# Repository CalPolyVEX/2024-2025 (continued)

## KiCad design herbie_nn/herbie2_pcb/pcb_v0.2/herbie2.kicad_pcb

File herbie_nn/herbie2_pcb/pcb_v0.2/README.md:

# Pinout

PA02 - unused analog input (A0)

PA04 - servo 3

PA05 - input voltage measurement

PA06 - right motor PWM

PA07 - left motor PWM

PA15 - servo 1

PA16 - left motor direction

PA17 - encoder 2 slave select

PA18 - right motor direction

PA19 - encoder 1 slave select

PA20 - servo 2

PA21 - servo 0

PB02 - unused analog input (A5)

PB08 - unused analog input (A1)

PB09 - unused analog input (A2)

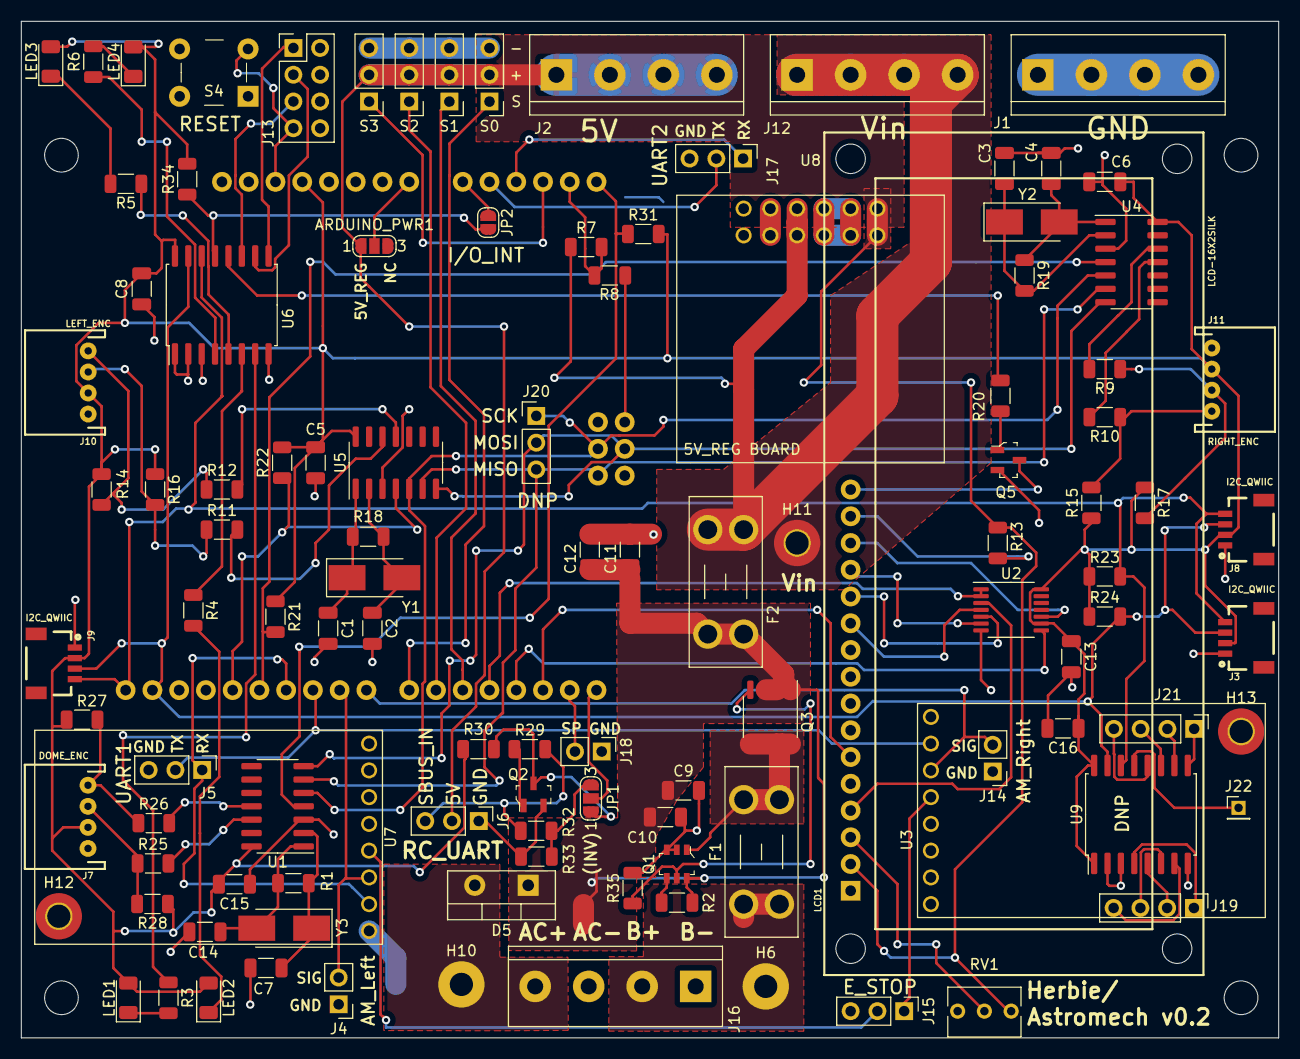
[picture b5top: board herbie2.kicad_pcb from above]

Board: 2 copper layers, 119.4 x 96.5 mm, 116 parts (1 on the bottom side), 92 nets.

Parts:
ARDUINO_PWR1: SolderJumper_3_Open; SolderJumper-3_P1.3mm_Open_RoundedPad1.0x1.5mm_NumberLabels
B2: ARDUINO_UNO_R3_SHIELD_ICSP; UNO_R3_SHIELD_ICSP
C1, C2, C3, C4, C7, C14: 12pF; C_1206_3216Metric
C5, C6, C8, C9, C13, C15, C16: .1uF; C_1206_3216Metric
C10: 1uF; C_1206_3216Metric
C11, C12: 10uF; C_1206_3216Metric
D5: CVFD20065A; TO-220-2_Vertical
F1, F2: Fuse; Fuseholder_Blade_Mini_Keystone_3568
H1, H2, H3, H4: MountingHole; MountingHole_3.2mm_M3_ISO7380
H6: PWR_BATT1; MountingHole_2.2mm_M2_Pad
H10: AC_PWR; MountingHole_2.2mm_M2_Pad
H11, H12, H13: MountingHole_Pad; MountingHole_2.2mm_M2_Pad_TopBottom
J1: GND; TerminalBlock_bornier-4_P5.08mm
J2: 5V; TerminalBlock_bornier-4_P5.08mm
J3, J8, J9: I2C_QWIIC; 1X04_1MM_RA
J4: AM_Left; PinHeader_1x02_P2.54mm_Vertical
J5: Conn_01x03_Female; PinHeader_1x03_P2.54mm_Vertical
J6: RC_UART; PinHeader_1x03_P2.54mm_Vertical
J7: DOME_ENC; JST-4-PTH
J10: LEFT_ENC; JST-4-PTH
J11: RIGHT_ENC; JST-4-PTH
J12: Vin; TerminalBlock_bornier-4_P5.08mm
J13: Conn_02x04_Odd_Even; PinHeader_2x04_P2.54mm_Vertical
J14: AM_Right; PinHeader_1x02_P2.54mm_Vertical
J15: Conn_01x03_Male; PinHeader_1x03_P2.54mm_Vertical
J16: Power; TerminalBlock_bornier-4_P5.08mm
J17, J20: Conn_01x03; PinHeader_1x03_P2.54mm_Vertical
J18: SmartPort; PinHeader_1x02_P2.54mm_Vertical
J19, J21: Conn_01x04_Female; PinHeader_1x04_P2.54mm_Vertical
J22: Conn_01x01; PinHeader_1x01_P2.00mm_Vertical
JP1: SolderJumper_3_Open; SolderJumper-3_P1.3mm_Open_RoundedPad1.0x1.5mm_NumberLabels
JP2: SolderJumper_2_Open; SolderJumper-2_P1.3mm_Open_RoundedPad1.0x1.5mm
LCD1: LCD-16X2SILK; LCD-16X2
LED1, LED2, LED3, LED4: LED; LED_1206_3216Metric
Q1: LTC4412; SOT-23-6
Q2, Q5: 2N7002; SOT-23-3
Q3: Si4427; SO-8_3.9x4.9mm_P1.27mm_Si4427
R1, R18, R19: 1M; R_1206_3216Metric
R2: 470K; R_1206_3216Metric
R3, R4, R5, R6: 330; R_1206_3216Metric
R7, R8: R; R_1206_3216Metric
R9, R10, R11, R12, R25, R26: 100; R_1206_3216Metric
R13: 10; R_1206_3216Metric
R14, R15, R16, R17, R21, R22, R27, R28, R31, R34: 20K; R_1206_3216Metric
R20, R29, R35: 1K; R_1206_3216Metric
R23, R24, R30, R32, R33: 4.7K; R_1206_3216Metric
RV1: 10K; Potentiometer_Bourns_3266Y_Vertical
S0: Servo0; PinHeader_1x03_P2.54mm_Vertical
S1: Servo1; PinHeader_1x03_P2.54mm_Vertical
S2: Servo2; PinHeader_1x03_P2.54mm_Vertical
S3: Servo3; PinHeader_1x03_P2.54mm_Vertical
S4: B3F-1000; Switch_Tactile_THT_B3F-1xxx
U1, U4, U5: LS7366R; SOIC-14_3.9x8.7mm_P1.27mm
U2: 74164; TSSOP-14_4.4x5mm_P0.65mm
U3, U7: 24v13_Pololu
U6, U9: TCA9534; SOIC-16W_7.5x10.3mm_P1.27mm
U8: D36V50F5_Pololu
Y1, Y2, Y3: 20MHz; Crystal_SMD_5032-2Pin_5.0x3.2mm_HandSoldering

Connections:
3.3V: B2.3.3V, C5.2, C6.2, C8.1, C13.1, C15.2, C16.1, J3.2, J7.2, J8.2, J9.2, J10.2, J11.2, LED1.2, LED2.2, LED3.2, LED4.2, R14.1, R15.1, R16.1, R17.1, R21.1, R22.2, R23.1, R24.1, R27.1, R28.1, R30.2, R31.2, R34.1, U1.14, U2.9, U2.14, U4.14, U5.14, U6.16, U9.1, U9.16
5V_REG: ARDUINO_PWR1.1, J2.1, J2.2, J2.3, J2.4, J6.2, LCD1.2, R13.1, RV1.1, S0.2, S1.2, S2.2, S3.2, U8.1
A0: B2.A0, JP2.1
AC_PWR: D5.2, H10.1, J16.4
ARD_VIN: ARDUINO_PWR1.2, B2.VIN
BATT1: F1.1, H6.1, J16.2
BATT1_F: F1.2, Q1.1, Q3.3
CLK_LCD: B2.D3, U2.8
DATA_LCD: B2.D4, U2.1, U2.2
DB4: LCD1.11, U2.4
DB5: LCD1.12, U2.5
DB6: LCD1.13, U2.6
DB7: LCD1.14, U2.10
DI0: J13.1, U6.9
DI1: J13.3, U6.10
DI2: J13.5, U6.11
ENC1_SS: B2.D12, R21.2, U4.4
ENC2_SS: B2.D13, R22.1, U5.4
ENC3_SS: B2.A5, R31.1, U1.4
ENC_MISO: B2.MISO, J20.3, U1.6, U4.6, U5.6
ENC_MOSI: B2.MOSI, J20.2, U1.7, U4.7, U5.7
ENC_SCK: B2.SCK, J20.1, U1.5, U4.5, U5.5
E_STOP1: J15.1, U3.4
E_STOP2: J15.2, U7.4
GND: B2.GND@, B2.GND_, C1.2, C2.2, C3.2, C4.2, C5.1, C6.1, C7.2, C8.2, C9.2, C10.2, C11.2, C12.2, C13.2, C14.2, C15.1, C16.2, H12.1, H13.1, J1.1, J1.2, J1.3, J1.4, J3.1, J4.1, J5.3, J6.1, J7.1, J8.1, J9.1, J10.1, J11.1, J13.2, J13.4, J13.6, J13.8, J14.1, J15.3, J16.1, J16.3, J17.3, J18.1, LCD1.1, LCD1.5, Q1.2, Q1.3, Q2.2, Q5.2, R8.2, R33.1, R35.2, RV1.3, S0.3, S1.3, S2.3, S3.3, S4.1, U1.3, U2.7, U3.1, U4.3, U5.3, U6.1, U6.2, U6.3, U6.8, U7.1, U8.2, U9.2, U9.3, U9.8
LCD_BL: R20.2, U6.12
LCD_E: B2.D2, LCD1.6
LCD_RS: LCD1.4, U2.3
MOTOR1_DIR: B2.D10, J5.2, U3.2
MOTOR1_PWM: B2.D8, J14.2, U3.3
MOTOR2_DIR: B2.D11, J5.1, U7.2
MOTOR2_PWM: B2.D9, J4.2, U7.3
unnamed: B2.A1, J17.2
unnamed: B2.A2, J17.1
unnamed: C1.1, R18.2, U5.1, Y1.1
unnamed: C2.1, R18.1, U5.2, Y1.2
unnamed: C3.1, R19.2, U4.2, Y2.1
unnamed: C4.1, R19.1, U4.1, Y2.2
unnamed: C7.1, R1.2, U1.2, Y3.1
unnamed: C14.1, R1.1, U1.1, Y3.2
unnamed: J7.3, R25.1, R28.2
unnamed: J7.4, R26.1, R27.2
unnamed: J10.3, R11.1, R16.2
unnamed: J10.4, R12.1, R14.2
unnamed: J11.3, R9.1, R17.2
unnamed: J11.4, R10.1, R15.2
unnamed: J19.1, U9.4
unnamed: J19.2, U9.5
unnamed: J19.3, U9.6
unnamed: J19.4, U9.7
unnamed: J21.1, U9.9
unnamed: J21.2, U9.10
unnamed: J21.3, U9.11
unnamed: J21.4, U9.12
unnamed: J22.1, U9.13
unnamed: JP1.1, Q2.3, R30.1
unnamed: JP2.2, R34.2, U6.13
unnamed: LCD1.3, RV1.2
unnamed: LCD1.15, R13.2
unnamed: LCD1.16, Q5.3
unnamed: LED1.1, R3.2
unnamed: LED2.1, R4.2
unnamed: LED3.1, R5.2
unnamed: LED4.1, R6.2
unnamed: Q1.4, R2.1
unnamed: Q1.5, Q3.1, R35.1
unnamed: Q2.1, R29.1
unnamed: Q5.1, R20.1
unnamed: R3.1, U6.7
unnamed: R4.1, U6.6
unnamed: R5.1, U6.5
unnamed: R6.1, U6.4
unnamed: R9.2, U4.12
unnamed: R10.2, U4.11
unnamed: R11.2, U5.12
unnamed: R12.2, U5.11
unnamed: R25.2, U1.12
unnamed: R26.2, U1.11
RESET: B2.RES, J13.7, S4.3
SBUS_IN: J6.3, R29.2, R32.2
SBUS_IN_SEL: B2.RX, JP1.2
SCL: B2.SCL, J3.4, J8.4, J9.4, R23.2, U6.14, U9.14
SDA: B2.SDA, J3.3, J8.3, J9.3, R24.2, U6.15, U9.15
SDIV: JP1.3, R32.1, R33.2
SERVO0: B2.D7, S0.1
SERVO1: B2.D5, S1.1
SERVO2: B2.D6, S2.1
SERVO3: B2.A3, S3.1
SMART_PORT: B2.TX, J18.2
VIN: F2.1, H11.1, J12.1, J12.2, J12.3, J12.4, R7.1, U8.3
VIN_FUSE: C9.1, C10.1, C11.1, C12.1, D5.1, F2.2, Q1.6, Q3.2, R2.2
VIN_MEASURE: B2.A4, R7.2, R8.1

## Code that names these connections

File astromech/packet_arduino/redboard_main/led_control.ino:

#include "led_control.h"

// LED Controller Uses Pin PA00 for RX and PA01 for TX

// Notes for PCB Connections:
// UART1 TX: D10 (PA18)
// UART1 RX: D11 (PA16)
// UART2 TX: A1 (PB08)
// UART2 RX: A2 (PB09)

// This Module Will Use UART2 TX with Sercom4, UART2 RX Will be Unused

// Data Transmission PseudoCode
// Have an Array of Size N Bytes to Contain the Data to be Transmitted
// This Array Should Have an Iterator That Contains the Current Byte to be Sent
// Upon Request to Send Packet, sendLEDCommand Will be Called.
// This Function Will Store The Data to be Transmitted, Its Size, Reset the Iterator, and Activate the First Byte to be Transmitted
// For Each Transmitted Byte that is Complete, an Interupt Will be Called, Requesting the Next Byte
// Increment the Iterator, but if Iterator Equals Packet Size, Stop Transmitting
// No Need for a Timer

// Array of Bytes
uint8_t transmit_bytes[8]{0};

// Index in Byte Array
uint8_t byte_index = 0;

// The Size of the Current Byte Packet
uint8_t packet_size = 0;

// Setup the USART for the LED Controller
void setupLED()
{
    PORT->Group[1].DIRSET.reg |= PORT_PB08;
    PORT->Group[1].OUTCLR.reg |= PORT_PB08;
    //PORT->Group[1].DIR.reg |= PORT_PB08;

    NVIC_DisableIRQ(SERCOM4_IRQn);

    // CLOCKING SERIAL
    GCLK->GENDIV.reg = GCLK_GENDIV_DIV(250) | // Divide the 48MHz clock source by divisor 1: 48MHz/1=48MHz
                       GCLK_GENDIV_ID(5);   // Select Generic Clock (GCLK) 5
    GCLK->GENCTRL.reg =
        GCLK_GENCTRL_IDC |
        GCLK_GENCTRL_GENEN |      // enable the clock connection to the peripheral(s)
        GCLK_GENCTRL_ID(5) |      // use clock gen 5
        GCLK_GENCTRL_SRC_DFLL48M; // Set Clock to 48 MHz
    GCLK->CLKCTRL.reg =
        GCLK_CLKCTRL_CLKEN |          // enable the clock
        GCLK_CLKCTRL_GEN_GCLK5 |      // enable generic clock generator 5
        GCLK_CLKCTRL_ID_SERCOM4_CORE; // set clock to SERCOM2_CORE

    SERCOM4->USART.CTRLA.bit.SWRST = 1; // do a software reset on the serial peripheral
    while (SERCOM4->USART.SYNCBUSY.bit.SWRST);

    // INITIALIZING PADS
    // initialize TX pin to be controlled by serial
    PORT->Group[1].PINCFG[8].bit.PMUXEN = 1; // designate RXPIN as controlled by a peripheral
    PORT->Group[1].PMUX[4].reg = PORT_PMUX_PMUXE_D; // set to use multiplexing D function

    
    
    // INITIALIZING SERIAL

    SERCOM4->USART.CTRLA.bit.MODE = 1;   // using internal clock
    SERCOM4->USART.CTRLA.bit.CMODE = 0;  // use asyncronous communication
    SERCOM4->USART.CTRLA.bit.SAMPR = 0x0;    // Set Serial to Arithmatic Mode
    SERCOM4->USART.CTRLA.bit.RXPO = 0x1; // Set Unused RX Pin to Pad[1]
    SERCOM4->USART.CTRLA.bit.TXPO = 0x0; // Set TX Pin to Pad[0]
    SERCOM4->USART.INTENCLR.bit.TXC = 0x1; // Set interupt to be disabled

    SERCOM4->USART.CTRLB.bit.CHSIZE = 0x0; // we have 8 bits of data per USART frame
    SERCOM4->USART.CTRLA.bit.DORD = 1;     // using MSB
    SERCOM4->USART.CTRLB.bit.SBMODE = 0x0; // using 1 stop bits
    SERCOM4->USART.BAUD.reg = 13107;       // Baud Rate for LED Controller is 9600
    SERCOM4->USART.CTRLB.bit.TXEN = 0x1;   // enable Serial TX
    SERCOM4->USART.CTRLB.bit.RXEN = 0x0; // turn RX pin off
    while (SERCOM4->USART.SYNCBUSY.bit.CTRLB); // wait for sync

    SERCOM4->USART.CTRLA.bit.ENABLE = 1; // enable the serial module

    while (SERCOM4->USART.SYNCBUSY.bit.ENABLE); // wait for syncronization

    // Enable the Transmit Complete Interupt
    NVIC_ClearPendingIRQ(SERCOM4_IRQn);                      // clear any incoming interrupt requests from SERCOM4
    NVIC_SetPriority(SERCOM4_IRQn, 0);                       // set highest priority for SERCOM4
    NVIC_EnableIRQ(SERCOM4_IRQn);                            // enable interrupt requests for SERCOM4
    SERCOM4->USART.INTENSET.reg = SERCOM_USART_INTENSET_TXC; // enable TXC interrupts for when recieving is complete

    // Reset Byte Index
    byte_index = 0;
}

// Send Command to LED Controller
void sendLEDCommand(uint8_t* package, uint8_t package_size)
{
    // Store Size of Package
    packet_size = package_size;

    // Copy Data of Package Parameter to Transmit Bytes Array
    //for (uint8_t* package_ptr = package, *bytes_ptr = transmit_bytes; package_ptr != package + packet_size; package_ptr++, bytes_ptr++)
    //    *bytes_ptr = *package_ptr;
    for (uint8_t i = 0; i < package_size; i++)
      transmit_bytes[i] = package[i];

    // Send First Byte
    SERCOM4->USART.DATA.bit.DATA = transmit_bytes[0];

    // Reset Byte Index
    byte_index = 1;
}

void SERCOM4_Handler()
{
    // Reset the Interupt Flag
    SERCOM4->USART.INTFLAG.bit.TXC = 0x1;
    PORT->Group[0].OUT.reg ^= PORT_PA17;

    // If Data is Still Left to be Transmitted, Transmit the Next Byte
    if (byte_index < packet_size)
    {
        SERCOM4->USART.DATA.bit.DATA = transmit_bytes[byte_index];
        byte_index++;
    }
}

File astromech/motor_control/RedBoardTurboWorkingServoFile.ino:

// C++ code
const uint32_t MOTOR_WAVELENGTH = 960000; //wavelength from peak to peak in Hz
const float MOTOR_BASE_TIME = 72000; //value in Hz of high length when speed = 0
const float MOTOR_CHANGE_CONST = 240; //multiplied by percentage to get change in range of wavelength needed
int motor_percentage_1 = 0; //range is -100 (100% backward) to 0 (0% speed) to 100 (100% forward) for left motor
int motor_percentage_2 = 0; //range is -100 (100% backward) to 0 (0% speed) to 100 (100% forward) for right motor

float theta = 0;

void setup() {
  // Set GCLK5's prescaler
    GCLK->GENDIV.reg = GCLK_GENDIV_DIV(1) | // Divide the 48MHz clock source by divisor 1: 48MHz/1=48MHz
                       GCLK_GENDIV_ID(5);   // Select Generic Clock (GCLK) 5
    while (GCLK->STATUS.bit.SYNCBUSY);

    // Configure GCLK5 to use DFLL48M
    GCLK->GENCTRL.reg = GCLK_GENCTRL_IDC |         // Set the duty cycle to 50/50 HIGH/LOW
                        GCLK_GENCTRL_GENEN |       // Enable GCLK5
                        GCLK_GENCTRL_SRC_DFLL48M | // Set the 48MHz clock source
                        GCLK_GENCTRL_ID(5);        // Select GCLK5
    while (GCLK->STATUS.bit.SYNCBUSY);

    // Connect GCLK5 to TCC0, TCC1
    GCLK->CLKCTRL.reg = GCLK_CLKCTRL_CLKEN |     // Enable GCLK5 to TCC0 and TCC1
                        GCLK_CLKCTRL_GEN_GCLK5 | // Select GCLK5
                        GCLK_CLKCTRL_ID_TCC0_TCC1; // Feed the GCLK5 to TCC0 and TCC1
    while (GCLK->STATUS.bit.SYNCBUSY);

    // Set prescaler TCCDiv for TCC1
    TCC1->CTRLA.reg |= TCC_CTRLA_PRESCALER(TCC_CTRLA_PRESCALER_DIV1_Val); //set prescalar to divide by 1

    //Use Normal PWM
    TCC1->WAVE.reg = TCC_WAVE_WAVEGEN_NPWM;
    while (TCC1->SYNCBUSY.bit.WAVE) {};

    //The PER register determines the period of the PWM
    //uint32_t period = 960000; //48000000/2400 = 20KHz

    TCC1->PER.reg = MOTOR_WAVELENGTH;  //this is a 24-bit register
    while (TCC1->SYNCBUSY.bit.PER) {};

    ///////////////////////////////
    //Left Motor

    //Set the duty cycle to controller speeds
    TCC1->CC[1].reg = MOTOR_BASE_TIME + (MOTOR_CHANGE_CONST * motor_percentage_1); //this set the on time of the PWM cycle based on the motor_percentage set by the controller
    while (TCC1->SYNCBUSY.bit.CC1) {};

    //set PA07 to output
    PORT->Group[0].DIRSET.reg = PORT_PA07; //set the direction to output
    PORT->Group[0].OUTCLR.reg = PORT_PA07; //set the value to output LOW

    /* Enable the peripheral multiplexer for the pins. */
    PORT->Group[0].PINCFG[7].reg |= PORT_PINCFG_PMUXEN;

    // Set PA07's function to function E. Function E is TCC1/WO[1] for PA07.
    // Because this is an odd numbered pin the PMUX is O (odd) and the PMUX
    // index is pin number - 1 / 2, so 3.
    PORT->Group[0].PMUX[3].reg = PORT_PMUX_PMUXO_E;

    //set motor dir PA16 to output
    PORT->Group[0].DIRSET.reg = PORT_PA16; //set the direction to output
    PORT->Group[0].OUTCLR.reg = PORT_PA16; //set the value to output LOW

    ///////////////////////////////
    //Right Motor
    //Set the duty cycle to controller speeds
    TCC1->CC[0].reg = MOTOR_BASE_TIME + (MOTOR_CHANGE_CONST * motor_percentage_2); //this set the on time of the PWM cycle based on the motor_percentage set by the controller
    while (TCC1->SYNCBUSY.bit.CC0) {};

    //set PA06 to output
    PORT->Group[0].DIRSET.reg = PORT_PA06; //set the direction to output
    PORT->Group[0].OUTCLR.reg = PORT_PA06; //set the value to output LOW

    /* Enable the peripheral multiplexer for the pins. */
    PORT->Group[0].PINCFG[6].reg |= PORT_PINCFG_PMUXEN;

    // Set PA06's function to function E. Function E is TCC1/WO[0] for PA06.
    // Because this is an even numbered pin the PMUX is E (even) and the PMUX
    // index is pin number / 2, so 3.
    PORT->Group[0].PMUX[3].reg |= PORT_PMUX_PMUXE_E;

    //set motor dir PA18 to output
    PORT->Group[0].DIRSET.reg = PORT_PA18; //set the direction to output
    PORT->Group[0].OUTCLR.reg = PORT_PA18; //set the value to output LOW

    ///////////////////////////////
    //Enable TCC1
    TCC1->CTRLA.reg |= (TCC_CTRLA_ENABLE);
    while (TCC1->SYNCBUSY.bit.ENABLE) {};
}

void loop() {
  // put your main code here, to run repeatedly:
  theta += 0.0001f;
  motor_percentage_1 = int(30*sin(theta));
  motor_percentage_2 = int(30*sin(theta + 3.14));

  TCC1->CC[0].reg = MOTOR_BASE_TIME + (MOTOR_CHANGE_CONST * motor_percentage_2); //this sets the on time of the PWM cycle
    while (TCC1->SYNCBUSY.bit.CC0) {};

  TCC1->CC[1].reg = MOTOR_BASE_TIME + (MOTOR_CHANGE_CONST * motor_percentage_1); //this set the on time of the PWM cycle
    while (TCC1->SYNCBUSY.bit.CC1) {};

}

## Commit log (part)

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2022-02-19 Updated Decoder File
2022-02-20 fixed packet, arduino side, now works, needs more testing
2022-02-20 fixed typos in packet, computer and arduino side
2022-03-05 added command 5 and some improvements
2022-04-02 Updated Servo Functionality
2022-04-23 Servos are now set to correct output pins
2022-04-23 Added RC decoding code
    initial addition
2022-05-07 made Redboard_Decoder slight modifications
    Originally the program was meant to be run with a processing program that visualized the channels. Modifications made make it so that just the arduino serial monitor can be used to monitor channels
2022-05-07 modified get_input
2022-05-13 python code to send data via serial
2022-05-14 moved register_blink
2022-05-14 RC Reciever now collects data
2022-05-21 started with rc decoding and cleaned up the code
2022-09-30 Create wiring overview
    Addition of a diagram focused on how wiring between components will work
2022-09-30 Create image version of wire overview
2022-10-01 refactored rc receiver code
2022-10-01 Moter Speed Has Been Lowered for Safety
2022-10-04 changed constant to more readable hex format
2022-10-04 Make sure the complete_packet buffer is reset (and invalid) after each properly received packet.
2022-10-04 Updated diagram
    added voltages
    added signal types
    separated signal and power wires
    removed main and accessories block, in practice the separation may be excessive and space-consuming
2022-10-08 rc_receiver controls motor correctly
2022-10-08 moved head motor encoder connection
2022-10-22 Issue #58: refactored packet arduino
2022-11-05 optimized speed of serial input for rc/pc switching
2022-11-12 finalization of pc/rc switching functionality
2022-11-12 fixed mistake in refactor
2022-11-12 Added Power Board Spreadsheet
2022-11-12 initial and functional implementation for controlling dome motor
2022-11-13 Update Parts List
2022-11-13 Created Board Files
2022-11-13 updated parts and added trace specs
2022-11-14 Updated board format
    PCB now has same form (size and mounting holes) as the control board
2022-11-15 removed spaces from pcb paths
    Also removed pcb backups folder, as we are using version control
2022-11-16 Delete Parts and Parameters Master.xlsx
    Has been moved to Google Sheets
2022-11-22 added inputs and outputs
    added power inputs and outputs, and made some simple connections
2022-11-29 Updated LTC7003 symbol
2022-11-30 added main switch LTC7003
    Generic symbols used. Not many symbols have associated footprints
2022-12-05 various circuit updates
2022-12-05 Added design/layout checklist
2022-12-05 updated checklist and neatened schematic
2022-12-05 Added mosfet footprint
2022-12-05 expanded regulator outputs to 4 outputs each
2022-12-05 Added Level Shifter
2022-12-05 Re-saved schematic
2022-12-06 switched LTC7003 input to resistive divider
2022-12-06 Renamed symbols in schematic
2022-12-06 Added grounded connections to level shifter
2022-12-06 Added Phoenix Contact screw terminal footprint
2022-12-06 added Molex screw terminal footprint
2022-12-06 Added battery wire solder-in
2022-12-06 Assigned more footprints
2022-12-06 Updated footprints with minor fixes
2022-12-06 loaded components into board
2022-12-06 grouped related components and did minor layout
2022-12-07 Removed board backups
2022-12-07 Assigned shottky diode footprints
2022-12-12 added LTC7003 current inrush limiting
2022-12-16 Modified level converter connections
    Made to fit NEO encoder connection order
2022-12-17 Assigned screw terminal to switch
2022-12-27 Added generic fuse footprint
2022-12-27 minor layout changes
    added trace to motor mosfet
2022-12-27 Updated generic fuse footprint
2022-12-27 Moved regulator fuses
    Moved regulator fuses to voltage input
2022-12-27 centered screw terminal footprints
2022-12-27 First fully routed board version
2023-01-14 LEDs Can now be Changed Through PC Commands
2023-01-21 added setupLed to packetArduino
2023-01-21 Fixed names for Logic Engine
2023-01-21 added LED control from PC
2023-01-27 partially updated power board
2023-01-28 revA done
2023-01-28 board wire bits removed
2023-02-01 changed fuse spacing
2023-02-07 check of revision A1 of the power board
2023-02-11 implemented support for onboard LEDs indicating control status
2023-02-17 initial checkin
2023-02-17 rename file
2023-02-17 modified packet parsing
2023-02-18 deleted old file
2023-02-18 Can Now Play Sounds Through Tsunami
2023-02-19 updated serial packet parsing
2023-02-19 serial test
2023-02-19 initialize the TCC0 timer
2023-02-19 code cleanup and documentation fixes
2023-02-20 update serial test script
2023-02-20 added startup blink
2023-02-23 sped up encoder interrupt
2023-02-25 Copied PSI Pro Code. Need to Review and Integrate
2023-02-28 fix spelling
2023-02-28 clean up code and remove define
2023-02-28 added serial packet table
2023-02-28 change the buffer size to a define
2023-02-28 add comment regarding baud computation
2023-03-02 Adjusted REON PC command ID for compatibility
2023-03-02 added install instructions
2023-03-04 added fix for Serial reference in TCA9534
2023-03-04 implemented pc support for REON holoprojectors
2023-03-04 Added a Function to Send Command to PSI Pro
2023-03-04 setup formatter
2023-03-04 implemented RC support for logic engine
2023-03-05 Prevents crash when LCD not connected
2023-03-05 84: setup vscode workspace
2023-03-07 revert LED function changes and add startup blink
2023-03-08 added timeout detection if the RC receiver is unplugged
2023-03-10 detect when lost frame packets are sent by the RC receiver
2023-03-10 updated cmd on pc side
2023-03-10 reset the queue on RC receiver errors
2023-03-10 working version of reverse byte decoding of SBUS packets
2023-03-11 added tsunami cmds
2023-03-11 fixed return values in buildmessage
2023-03-11 fixed volume
2023-03-11 Can Now Send PC Commands to Activate PSIs
2023-03-11 updated onboard LED macros
2023-03-11 Changed Motor Speed Between -100 and 100
2023-03-11 fixed set motor on pc side
2023-03-11 extra
2023-03-12 remove previous SBUS decoding function
2023-03-12 a better optimized version of decode that handles 8 bytes at a time
2023-03-13 reset the header and footer bytes for each new SBUS packet
2023-03-13 renamed variables for clarity and added comments
2023-03-14 reduce buffer queue size to less than 255 and rename variable
2023-03-14 added function to print all 16 channels to the LCD
2023-03-15 return false when an invalid SBUS packet is received
2023-04-08 added initial structure for PSI support to rc_data_collection
2023-04-15 first explorations for astromech debug mode
2023-04-29 Fixed Bugs with the Motors
2023-05-06 saving this while we flash new board
2023-05-13 implemented core debug mode program, added full support for holoprojector debugging
2023-05-20 implemented motor, servo, logic engine debug functionality
2023-06-01 Moved RC channels to working ones, changed RC LED to blinking, changed toggle constants, cleaned up code
2023-06-03 changed some logic engine variables for clarity
2023-06-06 added comments, can trigger sounds with switch and select sound with left stick
2023-06-13 add REON documentation notes
2023-08-07 working RC sound control and volume
2023-08-07 fixed indentation
2023-08-08 modified sound code
2023-10-14 Added Acceleration Control Code, Needs Testing
2023-10-14 Added Debug Function for Acceleration
2023-10-21 Now Able to Stop Songs After a Set Amount of Time
2023-10-21 Implemented state machine for rc button click
2023-10-21 Added double click hold
2023-10-22 finalized rc_tsunami. ready for new songs
2024-03-02 Fixed Packet Decoding on Arduino End
2024-04-06 Redboard Turbo Sends Data Back Through USB
2024-04-27 Ros2 network sending and recieving data at acceptable rate
2024-05-02 initial checkin of VEXU board
2024-05-04 added SAMD51 and encoder chips
2024-05-05 changed to SAMD51J19
2024-05-07 updated encoder chip
2024-05-09 added labels and logo
2024-05-10 added v0.1 reference design
2024-05-26 initial checkin of musty firmware
2024-05-26 added led file
2024-05-26 added encoders file and bootloader
2024-05-27 added level shifters for led strips
2024-05-30 encoder and led strip code
2024-06-10 updated send/receive to brain
2024-06-13 initial checkin of PROS test code
2024-06-20 refactor code
2024-10-05 added esp lib
2024-10-05 Add pros test board code
2024-10-06 update to Kicad 8.0 second try
2024-10-06 Delete astromech/Dome/Dome_Board/Dome_Board/Dome_Board-backups directory
    remove backup directory
2024-10-06 added qwiic connectors
2024-10-07 fixed ground disconnect
2024-10-07 v0.2 pre1
2024-10-08 Version 0.2 PCB
2024-10-12 added battery 5vRegulator 10/12
2024-10-13 changed code to have VEX brain request data
2024-10-13 changed brain code to request data from Musty board
2024-10-17 changed command size to 2 bytes
2024-10-17 changed command size on Musty board to 2 bytes
2024-10-18 adding pcb KiCAD files to ue4
2024-10-18 fixing file issues
2024-10-19 add some comments
2024-10-19 added optical tracking file and added comments
2024-10-19 added txd lp, rxd lp, pwd connectors
2024-10-19 added txd lp, rxd lp, PWM connectors
2024-10-22 added gitignore for backups
2024-10-22 added teensy audio
2024-10-22 removed backups
2024-10-25 added some new parts and updated symbols to fit better on schematic
2024-10-26 added more PWM and Servo driver
2024-10-28 gitignore update
2024-10-28 remove backup files
2024-11-02 added reset button
2024-11-06 initial checkin of Bluetooth serial code
2024-11-06 remove backup directory
2024-11-09 committing code for the mustyboard that does the VL53L0X sensor and has preliminary OTOS code.
2024-11-15 Checking in latest mustybaord demo code
2024-11-16 throwing mustyboard otos code in here that actually works
2024-11-30 Custom LemLib check-in (MustyLL). musty code is in lemblib::update, installed lvgl, circle chassis pos demo
2024-12-07 Add lvgl robot drawing + position to screen
2025-01-08 Remove build files
2025-01-08 Move files to root directory
2025-01-08 Code formatting and linting
2025-01-08 More unnecessary files
2025-01-08 Rename Project
2025-01-08 odomlocalspeed impl (first push didnt work), pathTest.txt placed in right spot (static), vex coord fix, conveyor_ctrls abstraction,
2025-01-08 mustyboard port added
2025-01-09 Cleaned up a lot of old comments, outlined TODOS in auto_state_machine.cpp, conveyor_ctrls.cpp, and main.cpp. made some changes to the fish mech conveyor method. implmemented setPose, which is a work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
2025-01-09 added comments and TODOS
2025-01-10 bug fixing with a lot of undefined methods and variables. color sorting clarificaions and fixes. moved drivetrain defns and PID defns to main.cpp. auto_stat_machine.h fix
2025-01-10 implemented mustyboard directional commands. the robot now can tell what direction it is in, given a ring color
2025-01-11 Set offset according to team
2025-01-11 PID TUNING 1/11/2025. swapped x and y to negatives in odom.cpp update() method
2025-01-13 moved things around, removed TODOS, and got tim's controls on repo.
2025-01-13 intake task fix
2025-01-14 comments, truncating
2025-01-14 color rejection works, as well as conveyor_move_to_pos
2025-01-16 Fix intake direction on green bot
2025-01-17 fixed hardware_map.h to be inline for all vars
2025-01-18 Add button manager (INCOMPLETE)
    This is a temp commit to view work on upcoming changes.
2025-01-18 PID tuning for lateral and angular. Issue fixed with sensor readings by using canned air and changing brake type to brake for auto. Created rudimentary path for robot to follow
2025-01-18 LemLib path testing
2025-01-27 WORKING DRIVE CODE
2025-01-28 adding Kelvin's stuff from PID testing
2025-01-28 drive fixes
2025-02-04 routine commit. working on mustyboard freezing bug
2025-02-08 Move hardware definitions to be extern
2025-02-08 pid as of now
2025-02-19 FISH MECH WORKS WOOOOOOOOOOOOOOOOOOOO
2025-02-22 Pushing PID values for angular and positional. Positional may need adjustment
2025-02-22 Fix prototype bot ports
2025-02-25 MB disconnect fixes, pointer decrement issue fix
2025-03-02 Add doinker class
2025-03-02 Add mogo grabber class
2025-03-02 Add fish mech class
